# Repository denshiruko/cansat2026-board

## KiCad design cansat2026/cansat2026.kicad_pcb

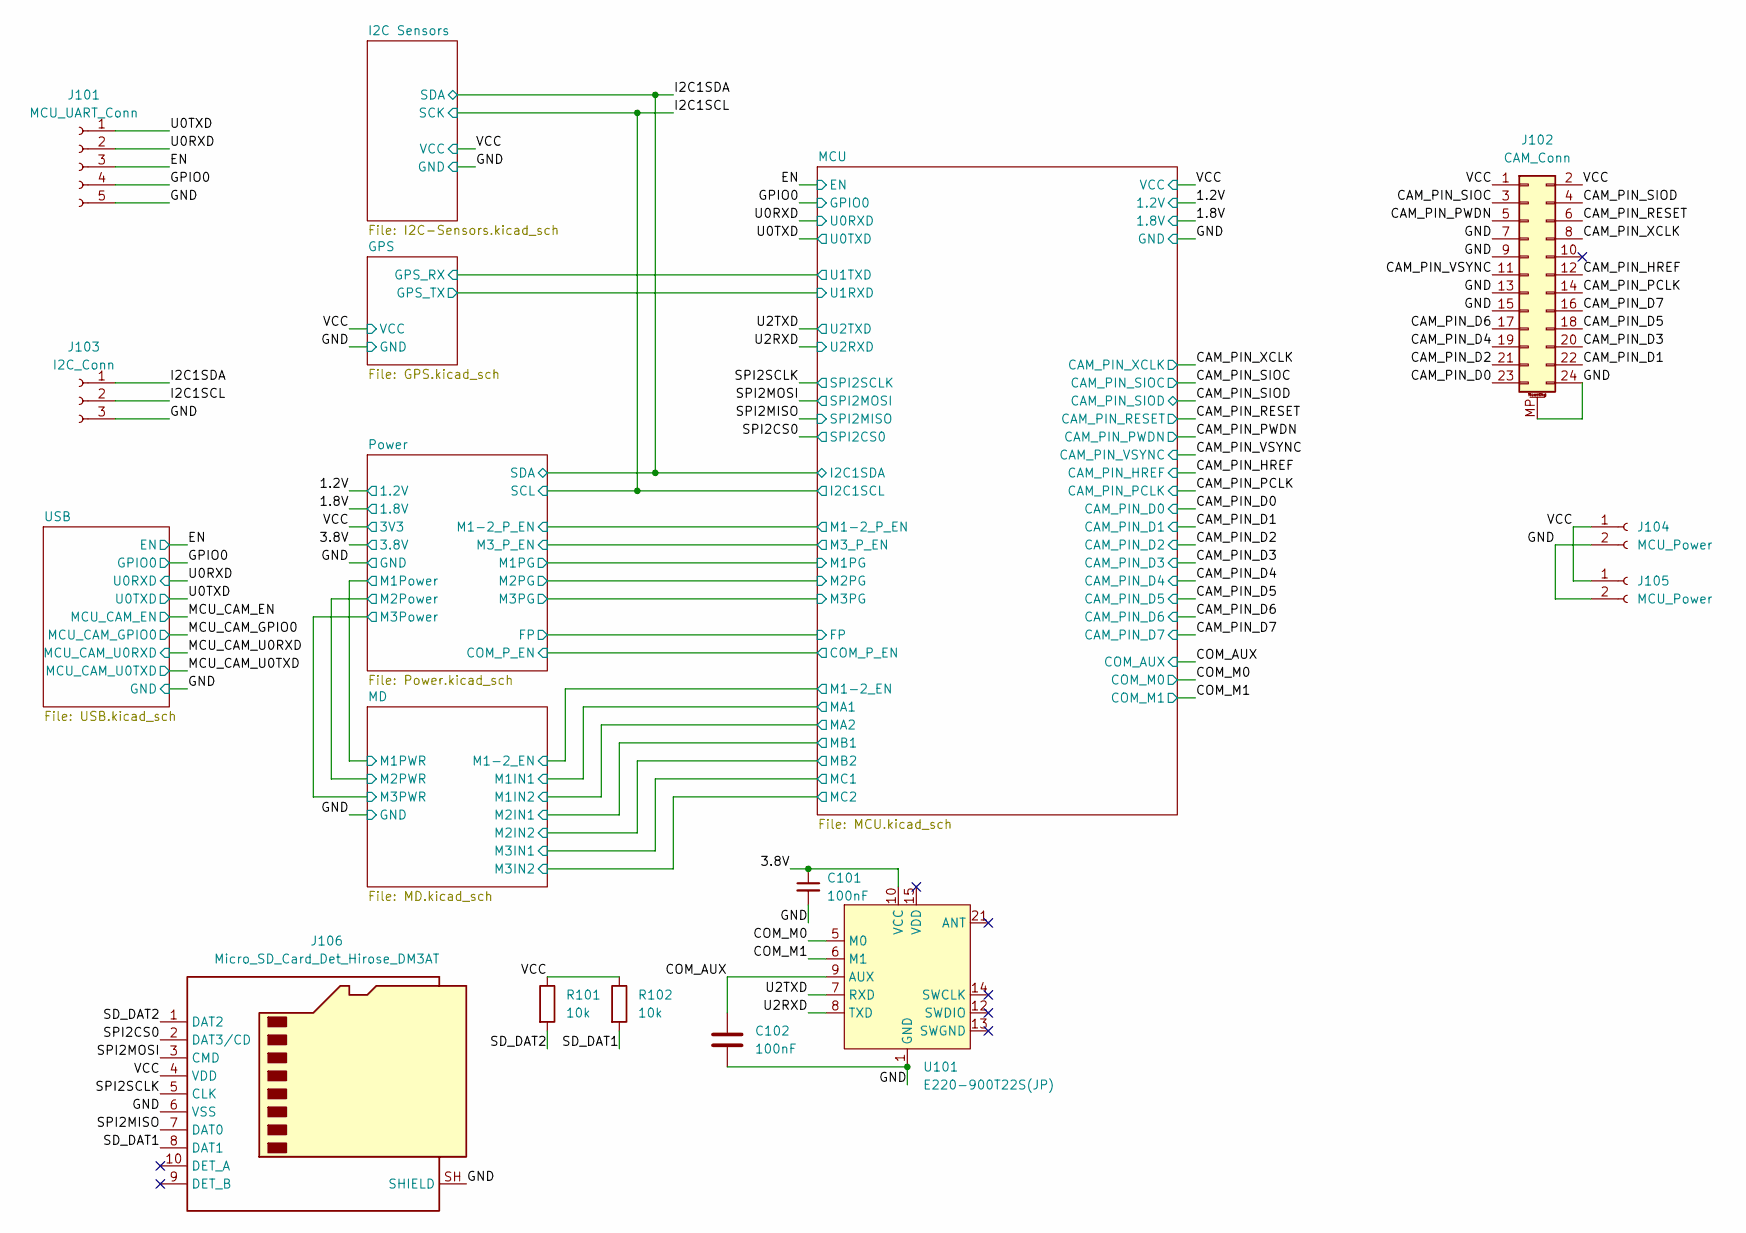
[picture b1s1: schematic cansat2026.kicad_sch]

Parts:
C101, C102: 100nF; C_0402_1005Metric; LCSC Part C1525
J101: MCU_UART_Conn; PinSocket_1x05_P2.54mm_Vertical
J102: CAM_Conn; SHOUHAN_XJH2.0_0.43-24P_1x24-1MP_P0.50mm_Horizontal; LCSC Part C5373439
J103: I2C_Conn; JST_XH_B3B-XH-A_1x03_P2.50mm_Vertical
J104, J105: MCU_Power; JST_XH_B2B-XH-A_1x02_P2.50mm_Vertical
J106: Micro_SD_Card_Det_Hirose_DM3AT; microSD_HC_Hirose_DM3AT-SF-PEJM5
R101, R102: 10k; R_0402_1005Metric; LCSC Part C25744
U101: E220-900T22S(JP)

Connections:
/3.8V: C101.1, U101.10 (VCC); also elsewhere on the board
/CAM_PIN_D0: J102.23; also elsewhere on the board
/CAM_PIN_D1: J102.22; also elsewhere on the board
/CAM_PIN_D2: J102.21; also elsewhere on the board
/CAM_PIN_D3: J102.20; also elsewhere on the board
/CAM_PIN_D4: J102.19; also elsewhere on the board
/CAM_PIN_D5: J102.18; also elsewhere on the board
/CAM_PIN_D6: J102.17; also elsewhere on the board
/CAM_PIN_D7: J102.16; also elsewhere on the board
/CAM_PIN_HREF: J102.12; also elsewhere on the board
/CAM_PIN_PCLK: J102.14; also elsewhere on the board
/CAM_PIN_PWDN: J102.5; also elsewhere on the board
/CAM_PIN_RESET: J102.6; also elsewhere on the board
/CAM_PIN_SIOC: J102.3; also elsewhere on the board
/CAM_PIN_SIOD: J102.4; also elsewhere on the board
/CAM_PIN_VSYNC: J102.11; also elsewhere on the board
/CAM_PIN_XCLK: J102.8; also elsewhere on the board
/COM_AUX: C102.1, U101.9 (AUX); also elsewhere on the board
/COM_M0: U101.5 (M0); also elsewhere on the board
/COM_M1: U101.6 (M1); also elsewhere on the board
/EN: J101.3; also elsewhere on the board
/GPIO0: J101.4; also elsewhere on the board
/I2C1SCL: J103.2; also elsewhere on the board
/I2C1SDA: J103.1; also elsewhere on the board
/SD_DAT1: J106.8 (DAT1), R102.2
/SD_DAT2: J106.1 (DAT2), R101.2
/SPI2CS0: J106.2 (DAT3/CD); also elsewhere on the board
/SPI2MISO: J106.7 (DAT0); also elsewhere on the board
/SPI2MOSI: J106.3 (CMD); also elsewhere on the board
/SPI2SCLK: J106.5 (CLK); also elsewhere on the board
/U0RXD: J101.2; also elsewhere on the board
/U0TXD: J101.1; also elsewhere on the board
/U2RXD: U101.8 (TXD); also elsewhere on the board
/U2TXD: U101.7 (RXD); also elsewhere on the board
/VCC: J102.1, J102.2, J104.1, J105.1, J106.4 (VDD), R101.1, R102.1; also elsewhere on the board
GND: C101.2, C102.2, J101.5, J102.7, J102.9, J102.13, J102.15, J102.24, J102.MP (MountPin), J103.3, J104.2, J105.2, J106.6 (VSS), J106.SH (SHIELD), U101.1 (GND), U101.2 (GND), U101.3 (GND), U101.4 (GND), U101.11 (GND), U101.19 (GND), U101.20 (GND), U101.22 (GND); also elsewhere on the board

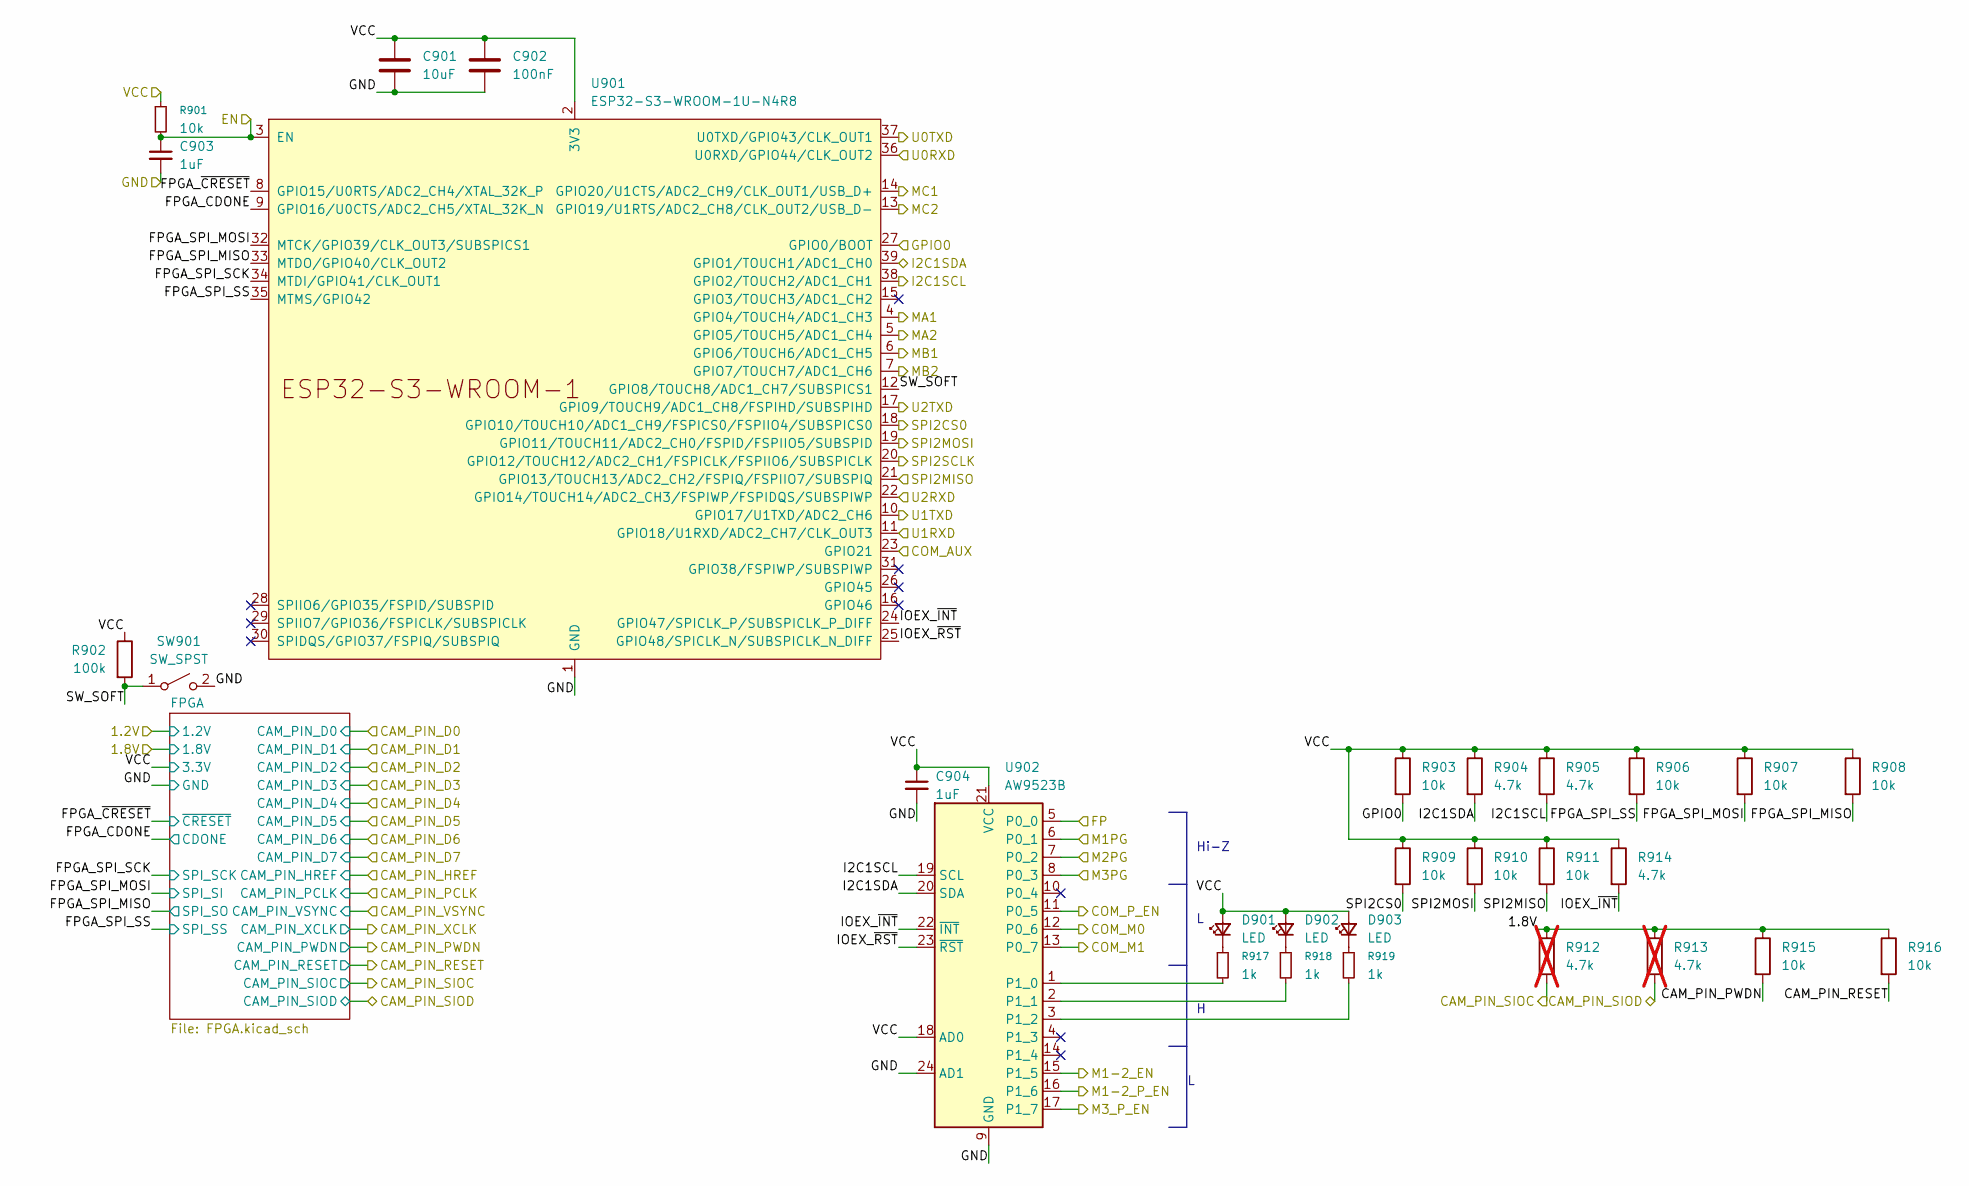
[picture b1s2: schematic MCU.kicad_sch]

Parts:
C901: 10uF; C_0402_1005Metric; LCSC Part C15525
C902: 100nF; C_0402_1005Metric; LCSC Part C1525
C903, C904: 1uF; C_0402_1005Metric; LCSC Part C52923
D901, D902, D903: LED; LED_0603_1608Metric
R901, R903, R906, R907, R908, R909, R910, R911, R915, R916: 10k; R_0402_1005Metric; LCSC Part C25744
R902: 100k; R_0402_1005Metric; LCSC Part C25741
R904, R905, R914: 4.7k; R_0402_1005Metric; LCSC Part C25900
R912, R913: 4.7k; R_0402_1005Metric; LCSC Part C25900; not fitted
R917, R918, R919: 1k; R_0402_1005Metric; LCSC Part C11702
SW901: SW_SPST; IS-1235-G
U901: ESP32-S3-WROOM-1U-N4R8; ESP32-S3-WROOM-1U; Mouser Part 356-ESP32S3WRM1UN4R8
U902: AW9523B; QFN-24-1EP_4x4mm_P0.5mm_EP2.7x2.7mm; LCSC Part C148077

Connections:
/1.8V: R912.1, R913.1, R915.1, R916.1; also elsewhere on the board
/CAM_PIN_PWDN: R915.2; also elsewhere on the board
/CAM_PIN_RESET: R916.2; also elsewhere on the board
/CAM_PIN_SIOC: R912.2; also elsewhere on the board
/CAM_PIN_SIOD: R913.2; also elsewhere on the board
/COM_AUX: U901.23 (GPIO21); also elsewhere on the board
/COM_M0: U902.12 (P0_6); also elsewhere on the board
/COM_M1: U902.13 (P0_7); also elsewhere on the board
/EN: C903.1, R901.2, U901.3 (EN); also elsewhere on the board
/GPIO0: R903.2, U901.27 (GPIO0/BOOT); also elsewhere on the board
/GPS/GPS_RX: U901.10 (GPIO17/U1TXD/ADC2_CH6); also elsewhere on the board
/GPS/GPS_TX: U901.11 (GPIO18/U1RXD/ADC2_CH7/CLK_OUT3); also elsewhere on the board
/I2C1SCL: R905.2, U901.38 (GPIO2/TOUCH2/ADC1_CH1), U902.19 (SCL); also elsewhere on the board
/I2C1SDA: R904.2, U901.39 (GPIO1/TOUCH1/ADC1_CH0), U902.20 (SDA); also elsewhere on the board
/MCU/COM_P_EN: U902.11 (P0_5); also elsewhere on the board
/MCU/FP: U902.5 (P0_0); also elsewhere on the board
/MCU/FPGA_CDONE: U901.9 (GPIO16/U0CTS/ADC2_CH5/XTAL_32K_N); also elsewhere on the board
/MCU/FPGA_SPI_MISO: R908.2, U901.33 (MTDO/GPIO40/CLK_OUT2); also elsewhere on the board
/MCU/FPGA_SPI_MOSI: R907.2, U901.32 (MTCK/GPIO39/CLK_OUT3/SUBSPICS1); also elsewhere on the board
/MCU/FPGA_SPI_SCK: U901.34 (MTDI/GPIO41/CLK_OUT1); also elsewhere on the board
/MCU/FPGA_SPI_SS: R906.2, U901.35 (MTMS/GPIO42); also elsewhere on the board
/MCU/FPGA_~CRESET: U901.8 (GPIO15/U0RTS/ADC2_CH4/XTAL_32K_P); also elsewhere on the board
/MCU/IOEX_~INT: R914.2, U901.24 (GPIO47/SPICLK_P/SUBSPICLK_P_DIFF), U902.22 (~INT)
/MCU/IOEX_~RST: U901.25 (GPIO48/SPICLK_N/SUBSPICLK_N_DIFF), U902.23 (~RST)
/MCU/M1-2_P_EN: U902.16 (P1_6); also elsewhere on the board
/MCU/M3_P_EN: U902.17 (P1_7); also elsewhere on the board
/MCU/MA1: U901.4 (GPIO4/TOUCH4/ADC1_CH3); also elsewhere on the board
/MCU/MA2: U901.5 (GPIO5/TOUCH5/ADC1_CH4); also elsewhere on the board
/MCU/MB1: U901.6 (GPIO6/TOUCH6/ADC1_CH5); also elsewhere on the board
/MCU/MB2: U901.7 (GPIO7/TOUCH7/ADC1_CH6); also elsewhere on the board
/MCU/MC1: U901.14 (GPIO20/U1CTS/ADC2_CH9/CLK_OUT1/USB_D+); also elsewhere on the board
/MCU/MC2: U901.13 (GPIO19/U1RTS/ADC2_CH8/CLK_OUT2/USB_D-); also elsewhere on the board
/MCU/SW_SOFT: R902.2, SW901.1 (A), U901.12 (GPIO8/TOUCH8/ADC1_CH7/SUBSPICS1)
/MD/M1-2_EN: U902.15 (P1_5); also elsewhere on the board
/Power/M1PG: U902.6 (P0_1); also elsewhere on the board
/Power/M2PG: U902.7 (P0_2); also elsewhere on the board
/Power/M3PG: U902.8 (P0_3); also elsewhere on the board
/SPI2CS0: R909.2, U901.18 (GPIO10/TOUCH10/ADC1_CH9/FSPICS0/FSPIIO4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); also elsewhere on the board
/SPI2MISO: R911.2, U901.21 (GPIO13/TOUCH13/ADC2_CH2/FSPIQ/FSPIIO7/S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); also elsewhere on the board
/SPI2MOSI: R910.2, U901.19 (GPIO11/TOUCH11/ADC2_CH0/FSPID/FSPIIO5/S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); also elsewhere on the board
/SPI2SCLK: U901.20 (GPIO12/TOUCH12/ADC2_CH1/FSPICLK/FSPIIO6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); also elsewhere on the board
/U0RXD: U901.36 (U0RXD/GPIO44/CLK_OUT2); also elsewhere on the board
/U0TXD: U901.37 (U0TXD/GPIO43/CLK_OUT1); also elsewhere on the board
/U2RXD: U901.22 (GPIO14/TOUCH14/ADC2_CH3/FSPIWP/FSPIDQS/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); also elsewhere on the board
/U2TXD: U901.17 (GPIO9/TOUCH9/ADC1_CH8/FSPIHD/SUBSPIHD); also elsewhere on the board
/VCC: C901.1, C902.1, C904.1, D901.2 (A), D902.2 (A), D903.2 (A), R901.1, R902.1, R903.1, R904.1, R905.1, R906.1, R907.1, R908.1, R909.1, R910.1, R911.1, R914.1, U901.2 (3V3), U902.18 (AD0), U902.21 (VCC); also elsewhere on the board
GND: C901.2, C902.2, C903.2, C904.2, SW901.2 (B), U901.1 (GND), U901.40 (GND), U901.41 (GND), U902.9 (GND), U902.24 (AD1), U902.25 (GND); also elsewhere on the board
unnamed: D901.1 (K), R917.1
unnamed: D902.1 (K), R918.1
unnamed: D903.1 (K), R919.1
unnamed: R917.2, U902.1 (P1_0)
unnamed: R918.2, U902.2 (P1_1)
unnamed: R919.2, U902.3 (P1_2)

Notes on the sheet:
Hi-Z

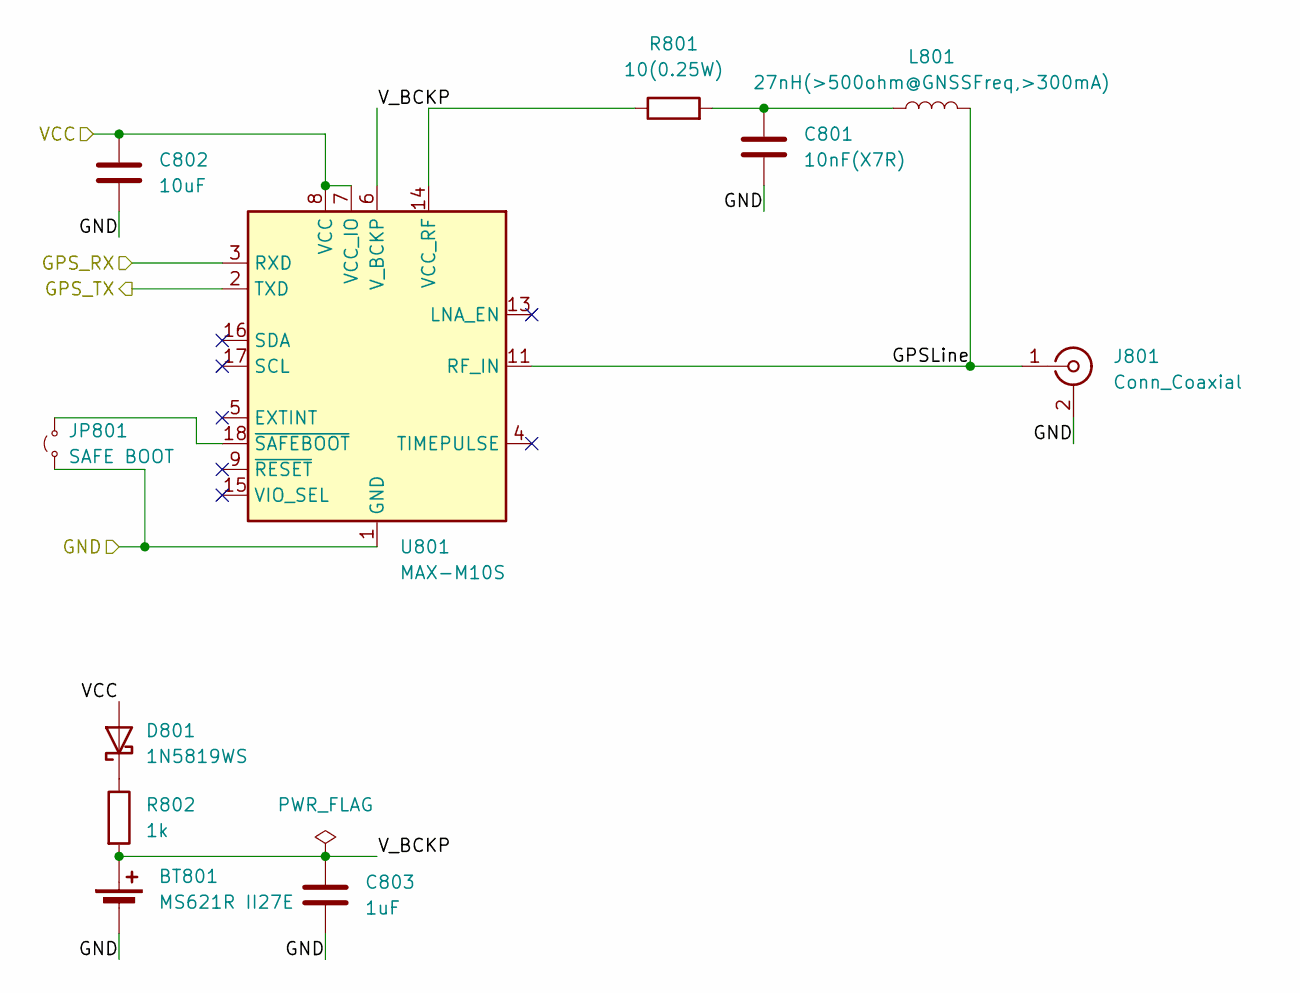
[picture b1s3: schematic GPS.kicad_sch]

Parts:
BT801: MS621R II27E; BAT_MS621R-II27E
C801: 10nF(X7R); C_0402_1005Metric; LCSC Part C15195
C802: 10uF; C_0402_1005Metric; LCSC Part C15525
C803: 1uF; C_0402_1005Metric; LCSC Part C52923
D801: 1N5819WS; D_SOD-323; LCSC Part C191023
J801: Conn_Coaxial; U.FL_Hirose_U.FL-R-SMT-1_Vertical
JP801: SAFE BOOT; SolderJumper-2_P1.3mm_Open_RoundedPad1.0x1.5mm
L801: 27nH(>500ohm@GNSSFreq,>300mA); L_0603_1608Metric; LCSC Part C148128
R801: 10(0.25W); R_1206_3216Metric; LCSC Part C17903
R802: 1k; R_0402_1005Metric; LCSC Part C11702
U801: MAX-M10S; ublox_MAX; DigiKey Part MAX-M10S-00B

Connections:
/GPS/GPSLine: J801.1 (In), L801.2, U801.11 (RF_IN)
/GPS/GPS_RX: U801.3 (RXD); also elsewhere on the board
/GPS/GPS_TX: U801.2 (TXD); also elsewhere on the board
/GPS/V_BCKP: BT801.1 (+), C803.1, R802.2, U801.6 (V_BCKP)
/VCC: C802.1, D801.2 (A), U801.7 (VCC_IO), U801.8 (VCC); also elsewhere on the board
GND: BT801.2 (-), C801.2, C802.2, C803.2, J801.2 (Ext), JP801.1 (A), U801.1 (GND), U801.10 (GND), U801.12 (GND); also elsewhere on the board
unnamed: C801.1, L801.1, R801.2
unnamed: D801.1 (K), R802.1
unnamed: JP801.2 (B), U801.18 (~SAFEBOOT)
unnamed: R801.1, U801.14 (VCC_RF)

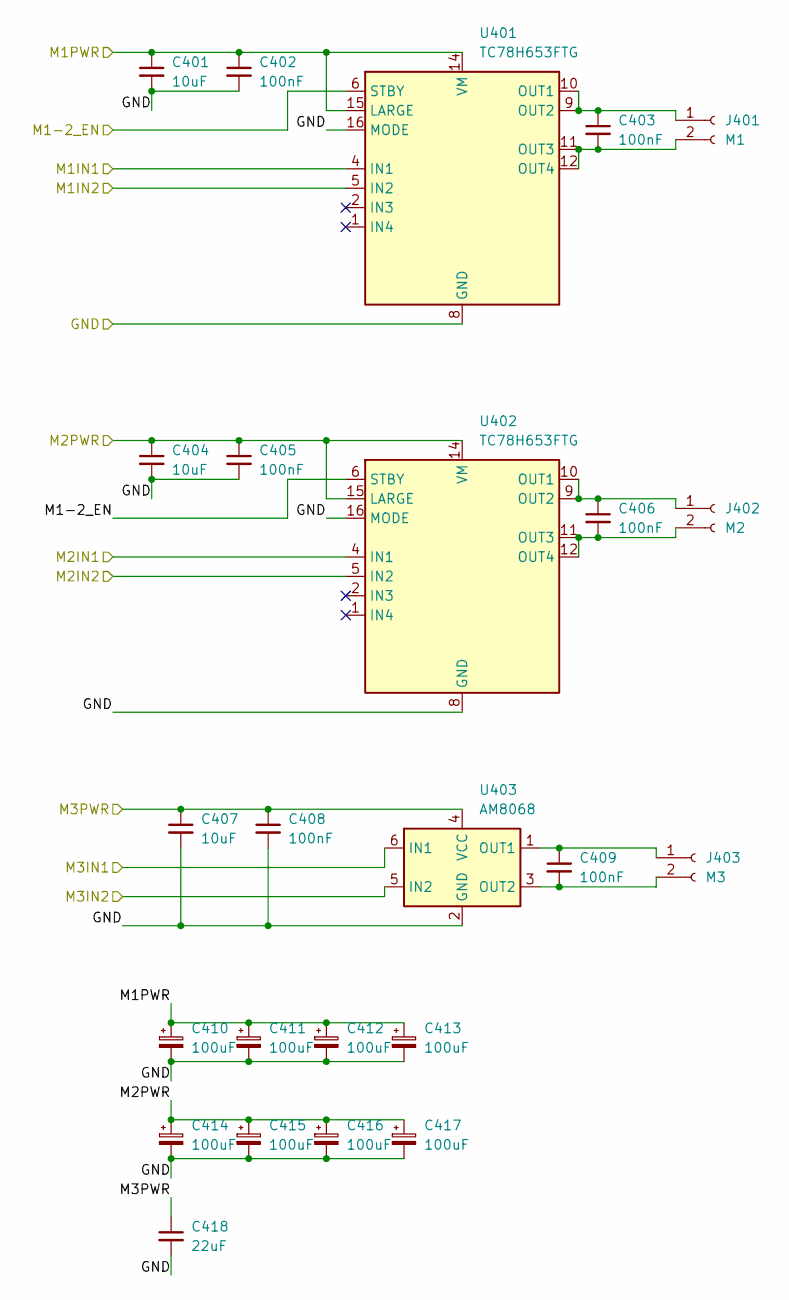
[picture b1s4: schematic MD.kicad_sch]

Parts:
C401, C404, C407: 10uF; C_0603_1608Metric; LCSC Part C19702
C402, C403, C405, C406, C408, C409: 100nF; C_0402_1005Metric; LCSC Part C1525
C410, C411, C412, C413, C414, C415, C416, C417: 100uF; MURATA_ECAS_D6
C418: 22uF; C_0805_2012Metric; LCSC Part C45783
J401: M1; JST_VH_B2P-VH_1x02_P3.96mm_Vertical
J402: M2; JST_VH_B2P-VH_1x02_P3.96mm_Vertical
J403: M3; JST_XH_B2B-XH-A_1x02_P2.50mm_Vertical
U401, U402: TC78H653FTG; VQFN-16-1EP_3x3mm_P0.5mm_EP1.8x1.8mm; LCSC Part C2150463
U403: AM8068; SOT-23-6

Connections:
/MCU/MA1: U401.4 (IN1); also elsewhere on the board
/MCU/MA2: U401.5 (IN2); also elsewhere on the board
/MCU/MB1: U402.4 (IN1); also elsewhere on the board
/MCU/MB2: U402.5 (IN2); also elsewhere on the board
/MCU/MC1: U403.6 (IN1); also elsewhere on the board
/MCU/MC2: U403.5 (IN2); also elsewhere on the board
/MD/M1-2_EN: U401.6 (STBY), U402.6 (STBY); also elsewhere on the board
/MD/M1PWR: C401.1, C402.1, C410.1, C411.1, C412.1, C413.1, U401.14 (VM), U401.15 (LARGE); also elsewhere on the board
/MD/M2PWR: C404.1, C405.1, C414.1, C415.1, C416.1, C417.1, U402.14 (VM), U402.15 (LARGE); also elsewhere on the board
/MD/M3PWR: C407.1, C408.1, C418.1, U403.4 (VCC); also elsewhere on the board
GND: C401.2, C402.2, C404.2, C405.2, C407.2, C408.2, C410.2, C411.2, C412.2, C413.2, C414.2, C415.2, C416.2, C417.2, C418.2, U401.8 (GND), U401.13 (GND), U401.16 (MODE), U401.17 (GND), U402.8 (GND), U402.13 (GND), U402.16 (MODE), U402.17 (GND), U403.2 (GND); also elsewhere on the board
unnamed: C403.1, J401.1, U401.9 (OUT2), U401.10 (OUT1)
unnamed: C403.2, J401.2, U401.11 (OUT3), U401.12 (OUT4)
unnamed: C406.1, J402.1, U402.9 (OUT2), U402.10 (OUT1)
unnamed: C406.2, J402.2, U402.11 (OUT3), U402.12 (OUT4)
unnamed: C409.1, J403.1, U403.1 (OUT1)
unnamed: C409.2, J403.2, U403.3 (OUT2)

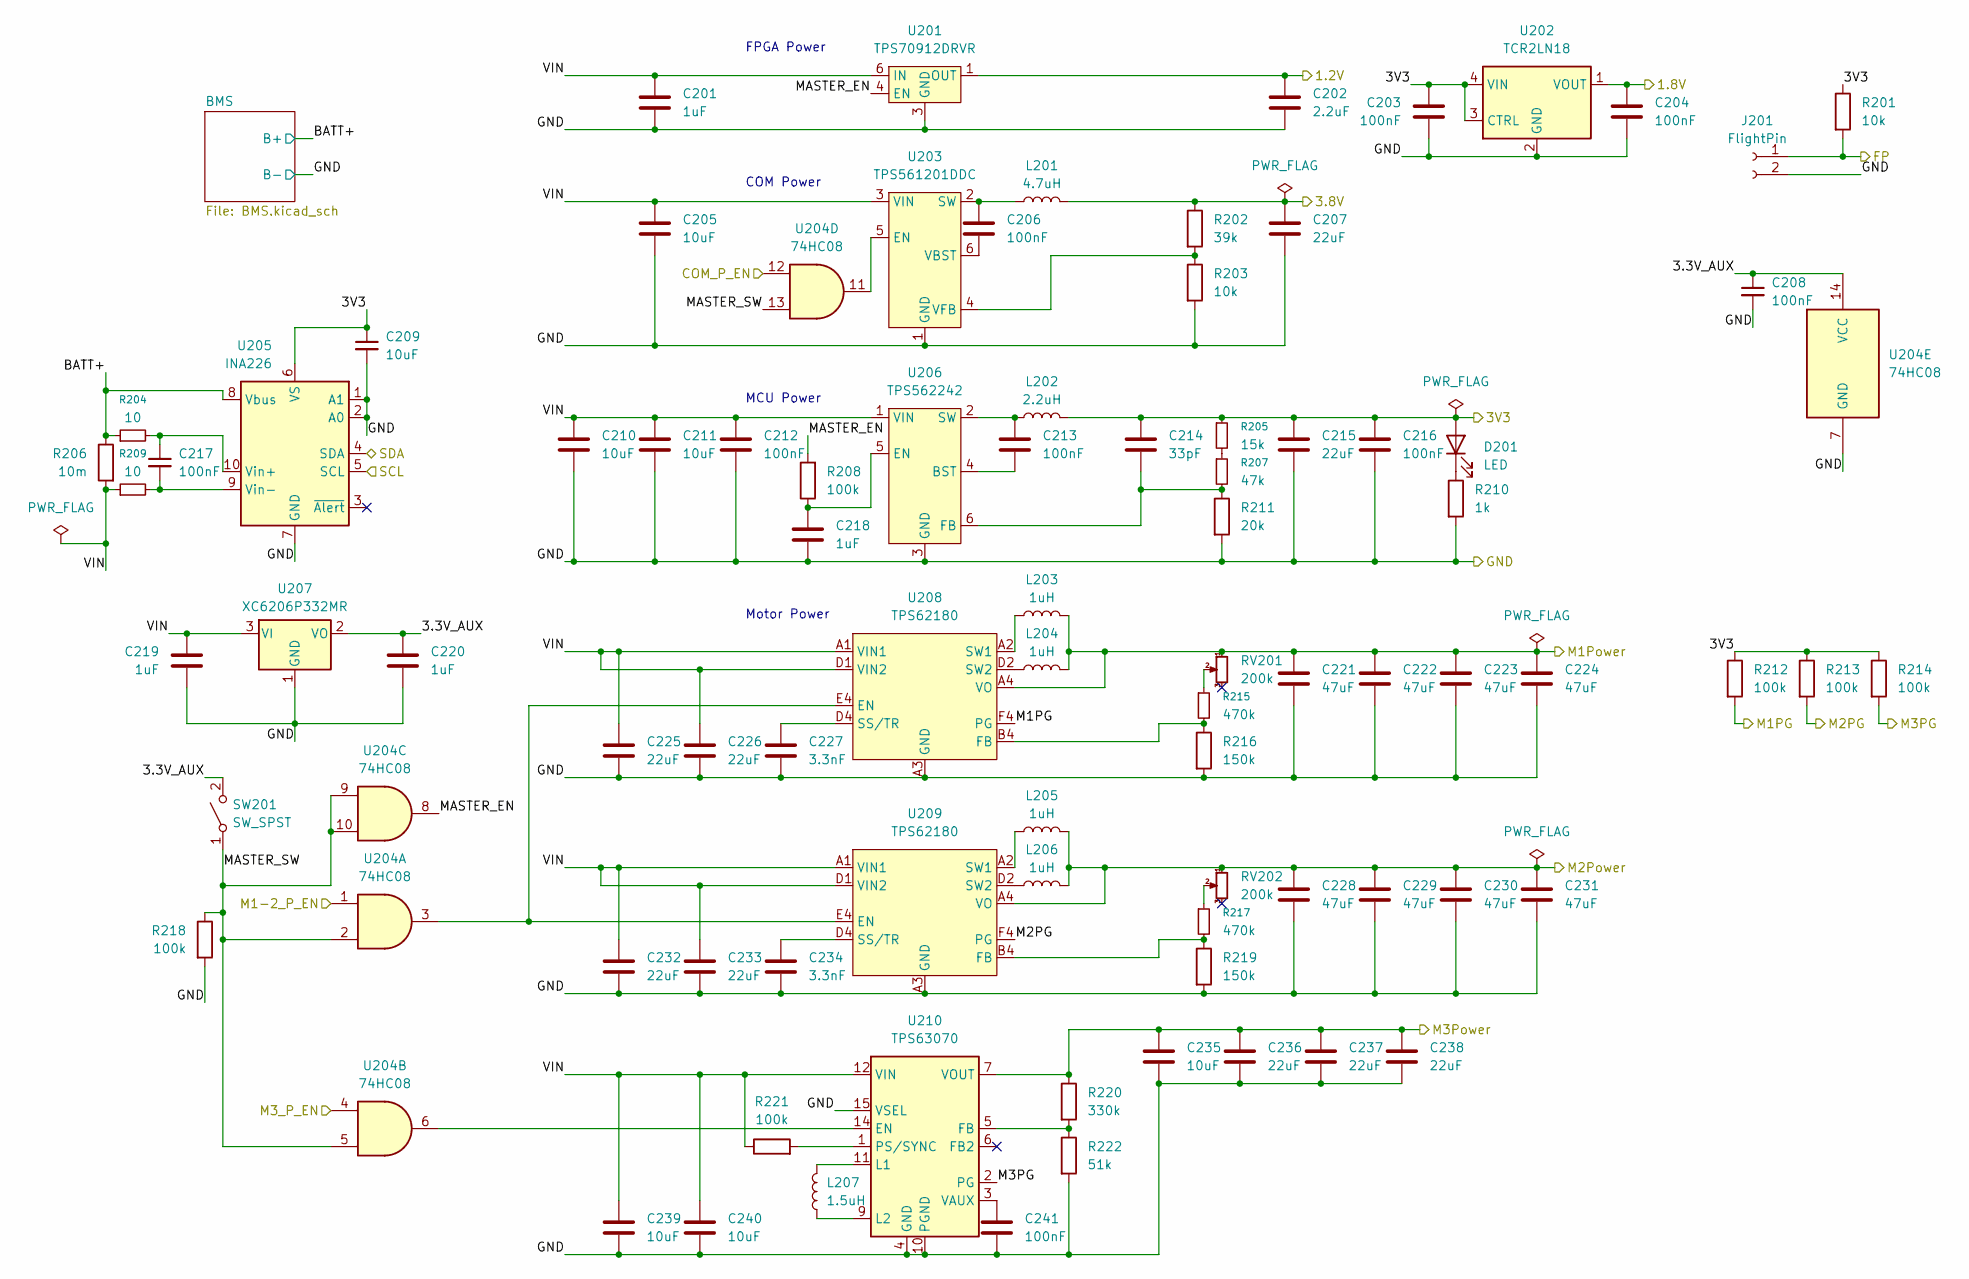
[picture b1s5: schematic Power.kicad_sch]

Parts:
C201, C218, C219, C220: 1uF; C_0402_1005Metric; LCSC Part C52923
C202: 2.2uF; C_0402_1005Metric; LCSC Part C12530
C203, C204, C206, C208, C212, C213, C216, C217, C241: 100nF; C_0402_1005Metric; LCSC Part C1525
C205, C210, C211, C235, C239, C240: 10uF; C_0805_2012Metric; LCSC Part C15850
C207, C215, C225, C226, C232, C233, C236, C237, C238: 22uF; C_0805_2012Metric; LCSC Part C45783
C209: 10uF; C_0402_1005Metric; LCSC Part C15525
C214: 33pF; C_0402_1005Metric; LCSC Part C1562
C221, C222, C223, C224, C228, C229, C230, C231: 47uF; C_0805_2012Metric; LCSC Part C16780
C227, C234: 3.3nF; C_0603_1608Metric; LCSC Part C1613
D201: LED; LED_0603_1608Metric
J201: FlightPin; JST_XH_B2B-XH-A_1x02_P2.50mm_Vertical
L201: 4.7uH; L_1008_2520Metric_Pad1.43x2.20mm_HandSolder; DigiKey Part WIP252012S-4R7MLDG
L202: 2.2uH; L_Taiyo-Yuden_NR-50xx_HandSoldering; Mouser Part 963-LSXND5050WDL2R2N
L203, L204, L205, L206: 1uH; L_Taiyo-Yuden_LSEU-4040; Mouser Part 963-LSEUB4040WKT1R0M
L207: 1.5uH; L_Wuerth_PMCI-201610; DigiKey Part WIP201610S-1R5MLDG
R201, R203: 10k; R_0402_1005Metric; LCSC Part C25744
R202: 39k; R_0402_1005Metric; LCSC Part C25783
R204, R209: 10; R_0402_1005Metric; LCSC Part C25077
R205: 15k; R_0402_1005Metric; LCSC Part C25756
R206: 10m; R_1206_3216Metric; LCSC Part C20160275
R207: 47k; R_0402_1005Metric; LCSC Part C25792
R208, R212, R213, R214, R218, R221: 100k; R_0402_1005Metric; LCSC Part C25741
R210: 1k; R_0402_1005Metric; LCSC Part C11702
R211: 20k; R_0402_1005Metric; LCSC Part C25765
R215, R217: 470k; R_0402_1005Metric; LCSC Part C25790
R216, R219: 150k; R_0402_1005Metric; LCSC Part C25755
R220: 330k; R_0402_1005Metric; LCSC Part C25778
R222: 51k; R_0402_1005Metric; LCSC Part C25794
RV201, RV202: 200k; Potentiometer_Bourns_TC33X_Vertical; DigiKey Part TC33X-2-204E
SW201: SW_SPST; SW_DIP_SPSTx01_Slide_6.7x4.1mm_W8.61mm_P2.54mm_LowProfile; DigiKey Part DS04-254-1-01BK-SMT
U201: TPS70912DRVR; WSON-6-1EP_2x2mm_P0.65mm_EP1x1.6mm; LCSC Part C2863472
U202: TCR2LN18; SDFN4; LCSC Part C7360727
U203: TPS561201DDC; SOT-23-6; LCSC Part C220433
U204: 74HC08; SOIC-14_3.9x8.7mm_P1.27mm; LCSC Part C5593
U205: INA226; TSSOP-10_3x3mm_P0.5mm; LCSC Part C49851
U206: TPS562242; SOT-563; LCSC Part C19272253
U207: XC6206P332MR; SOT-23-3; LCSC Part C5446
U208, U209: TPS62180; TPS62180YZF; LCSC Part C2071394
U210: TPS63070; QFN-16_2.4x2.9_Pitch0.5mm; LCSC Part C2072046

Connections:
/1.2V: C202.1, U201.1 (OUT); also elsewhere on the board
/1.8V: C204.1, U202.1 (VOUT); also elsewhere on the board
/3.8V: C207.1, L201.2, R202.1; also elsewhere on the board
/I2C1SCL: U205.5 (SCL); also elsewhere on the board
/I2C1SDA: U205.4 (SDA); also elsewhere on the board
/MCU/COM_P_EN: U204.12; also elsewhere on the board
/MCU/FP: J201.1, R201.2; also elsewhere on the board
/MCU/M1-2_P_EN: U204.1; also elsewhere on the board
/MCU/M3_P_EN: U204.4; also elsewhere on the board
/MD/M1PWR: C221.1, C222.1, C223.1, C224.1, L203.2, L204.2, RV201.1, U208.A4 (VO); also elsewhere on the board
/MD/M2PWR: C228.1, C229.1, C230.1, C231.1, L205.2, L206.2, RV202.1, U209.A4 (VO); also elsewhere on the board
/MD/M3PWR: C235.1, C236.1, C237.1, C238.1, R220.1, U210.7 (VOUT), U210.8 (VOUT); also elsewhere on the board
/Power/3.3V_AUX: C208.1, C220.1, SW201.2 (B), U204.14 (VCC), U207.2 (VO)
/Power/BATT+: R204.1, R206.1, U205.8 (Vbus); also elsewhere on the board
/Power/M1PG: R212.2, U208.F4 (PG); also elsewhere on the board
/Power/M2PG: R213.2, U209.F4 (PG); also elsewhere on the board
/Power/M3PG: R214.2, U210.2 (PG); also elsewhere on the board
/Power/MASTER_EN: R208.2, U201.4 (EN), U204.8
/Power/MASTER_SW: R218.1, SW201.1 (A), U204.2, U204.5, U204.9, U204.10, U204.13
/VCC: C203.1, C209.1, C214.1, C215.1, C216.1, D201.2 (A), L202.2, R201.1, R205.1, R212.1, R213.1, R214.1, U202.3 (CTRL), U202.4 (VIN), U205.6 (VS); also elsewhere on the board
GND: C201.2, C202.2, C203.2, C204.2, C205.2, C207.2, C208.2, C209.2, C210.2, C211.2, C212.2, C215.2, C216.2, C218.2, C219.2, C220.2, C221.2, C222.2, C223.2, C224.2, C225.2, C226.2, C227.2, C228.2, C229.2, C230.2, C231.2, C232.2, C233.2, C234.2, C235.2, C236.2, C237.2, C238.2, C239.2, C240.2, C241.2, J201.2, R203.2, R210.2, R211.2, R216.2, R218.2, R219.2, R222.2, U201.3 (GND), U201.7 (GND), U202.2 (GND), U203.1 (GND), U204.7 (GND), U205.1 (A1), U205.2 (A0), U205.7 (GND), U206.3 (GND), U207.1 (GND), U208.A3 (GND), U208.B3 (GND), U208.C3 (GND), U208.C4 (GND), U208.D3 (GND), U208.E3 (GND), U208.F3 (GND), U209.A3 (GND), U209.B3 (GND), U209.C3 (GND), U209.C4 (GND), U209.D3 (GND), U209.E3 (GND), U209.F3 (GND), U210.4 (GND), U210.10 (PGND), U210.15 (VSEL); also elsewhere on the board
unnamed: D201.1 (K), R210.1
unnamed: L203.1, U208.A2 (SW1), U208.B2 (SW1), U208.C2 (SW1)
unnamed: L204.1, U208.D2 (SW2), U208.E2 (SW2), U208.F2 (SW2)
unnamed: L205.1, U209.A2 (SW1), U209.B2 (SW1), U209.C2 (SW1)
unnamed: L206.1, U209.D2 (SW2), U209.E2 (SW2), U209.F2 (SW2)
unnamed: R205.2, R207.1
unnamed: R215.1, RV201.2
unnamed: R217.1, RV202.2
unnamed: U203.5 (EN), U204.11
unnamed: C206.1, L201.1, U203.2 (SW)
unnamed: C206.2, U203.6 (VBST)
unnamed: R202.2, R203.1, U203.4 (VFB)
unnamed: C217.1, R204.2, U205.10 (Vin+)
unnamed: C217.2, R209.2, U205.9 (Vin-)
unnamed: C213.2, U206.4 (BST)
unnamed: C218.1, R208.1, U206.5 (EN)
unnamed: C214.2, R207.2, R211.1, U206.6 (FB)
unnamed: C213.1, L202.1, U206.2 (SW)
unnamed: U204.3, U208.E4 (EN), U209.E4 (EN)
unnamed: R215.2, R216.1, U208.B4 (FB)
unnamed: C227.1, U208.D4 (SS/TR)
unnamed: R217.2, R219.1, U209.B4 (FB)
unnamed: C234.1, U209.D4 (SS/TR)
unnamed: U204.6, U210.14 (EN)
unnamed: R220.2, R222.1, U210.5 (FB)
unnamed: L207.2, U210.11 (L1)
unnamed: L207.1, U210.9 (L2)
unnamed: R221.2, U210.1 (PS/SYNC)
unnamed: C241.1, U210.3 (VAUX)
VIN: C201.1, C205.1, C210.1, C211.1, C212.1, C219.1, C225.1, C226.1, C232.1, C233.1, C239.1, C240.1, R206.2, R209.1, R221.1, U201.6 (IN), U203.3 (VIN), U206.1 (VIN), U207.3 (VI), U208.A1 (VIN1), U208.B1 (VIN1), U208.C1 (VIN1), U208.D1 (VIN2), U208.E1 (VIN2), U208.F1 (VIN2), U209.A1 (VIN1), U209.B1 (VIN1), U209.C1 (VIN1), U209.D1 (VIN2), U209.E1 (VIN2), U209.F1 (VIN2), U210.12 (VIN), U210.13 (VIN)

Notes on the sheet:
COM Power
FPGA Power
MCU Power
Motor Power

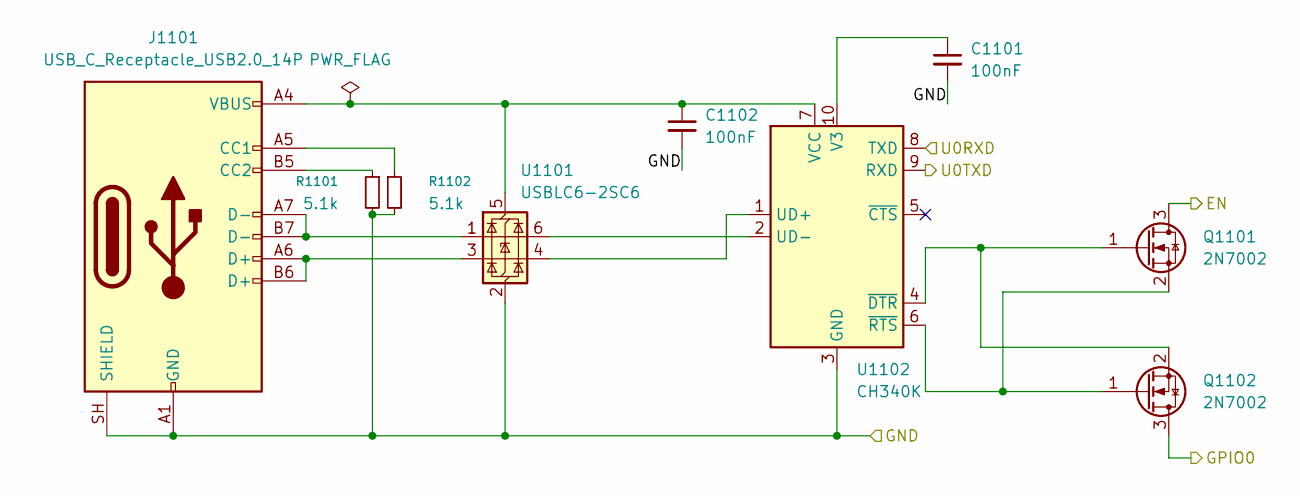
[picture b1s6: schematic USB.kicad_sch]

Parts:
C1101, C1102: 100nF; C_0402_1005Metric; LCSC Part C1525
J1101: USB_C_Receptacle_USB2.0_14P; USB_C_Receptacle_GCT_USB4105-xx-A_16P_TopMnt_Horizontal; LCSC Part C36936538
Q1101, Q1102: 2N7002; SOT-23; LCSC Part C8545
R1101, R1102: 5.1k; R_0402_1005Metric; LCSC Part C25905
U1101: USBLC6-2SC6; SOT-23-6; LCSC Part C5180249
U1102: CH340K; SSOP-10-1EP_3.9x4.9mm_P1mm_EP2.1x3.3mm

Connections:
/EN: Q1101.3 (D); also elsewhere on the board
/GPIO0: Q1102.3 (D); also elsewhere on the board
/U0RXD: U1102.8 (TXD); also elsewhere on the board
/U0TXD: U1102.9 (RXD); also elsewhere on the board
GND: C1101.2, C1102.2, J1101.A1 (GND), J1101.A12 (GND), J1101.B1 (GND), J1101.B12 (GND), J1101.SH (SHIELD), R1101.2, R1102.2, U1101.2 (GND), U1102.3 (GND), U1102.11 (GND); also elsewhere on the board
unnamed: J1101.A5 (CC1), R1102.1
unnamed: J1101.B5 (CC2), R1101.1
unnamed: J1101.A6 (D+), J1101.B6 (D+), U1101.3 (I/O2)
unnamed: J1101.A7 (D-), J1101.B7 (D-), U1101.1 (I/O1)
unnamed: Q1101.1 (G), Q1102.2 (S), U1102.4 (~DTR)
unnamed: Q1101.2 (S), Q1102.1 (G), U1102.6 (~RTS)
unnamed: C1102.1, J1101.A4 (VBUS), J1101.A9 (VBUS), J1101.B4 (VBUS), J1101.B9 (VBUS), U1101.5 (VBUS), U1102.7 (VCC)
unnamed: U1101.4 (I/O2), U1102.1 (UD+)
unnamed: U1101.6 (I/O1), U1102.2 (UD-)
unnamed: C1101.1, U1102.10 (V3)
